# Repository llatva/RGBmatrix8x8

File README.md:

# RGBmatrix8x8
8x8 RGB matrix based on WS2813B addressable RGB leds

By Lasse Latva OH3HZB (2022)

This work is licensed under: Creative Commons Attribution 4.0 International (CC BY 4.0) https://creativecommons.org/licenses/by/4.0/

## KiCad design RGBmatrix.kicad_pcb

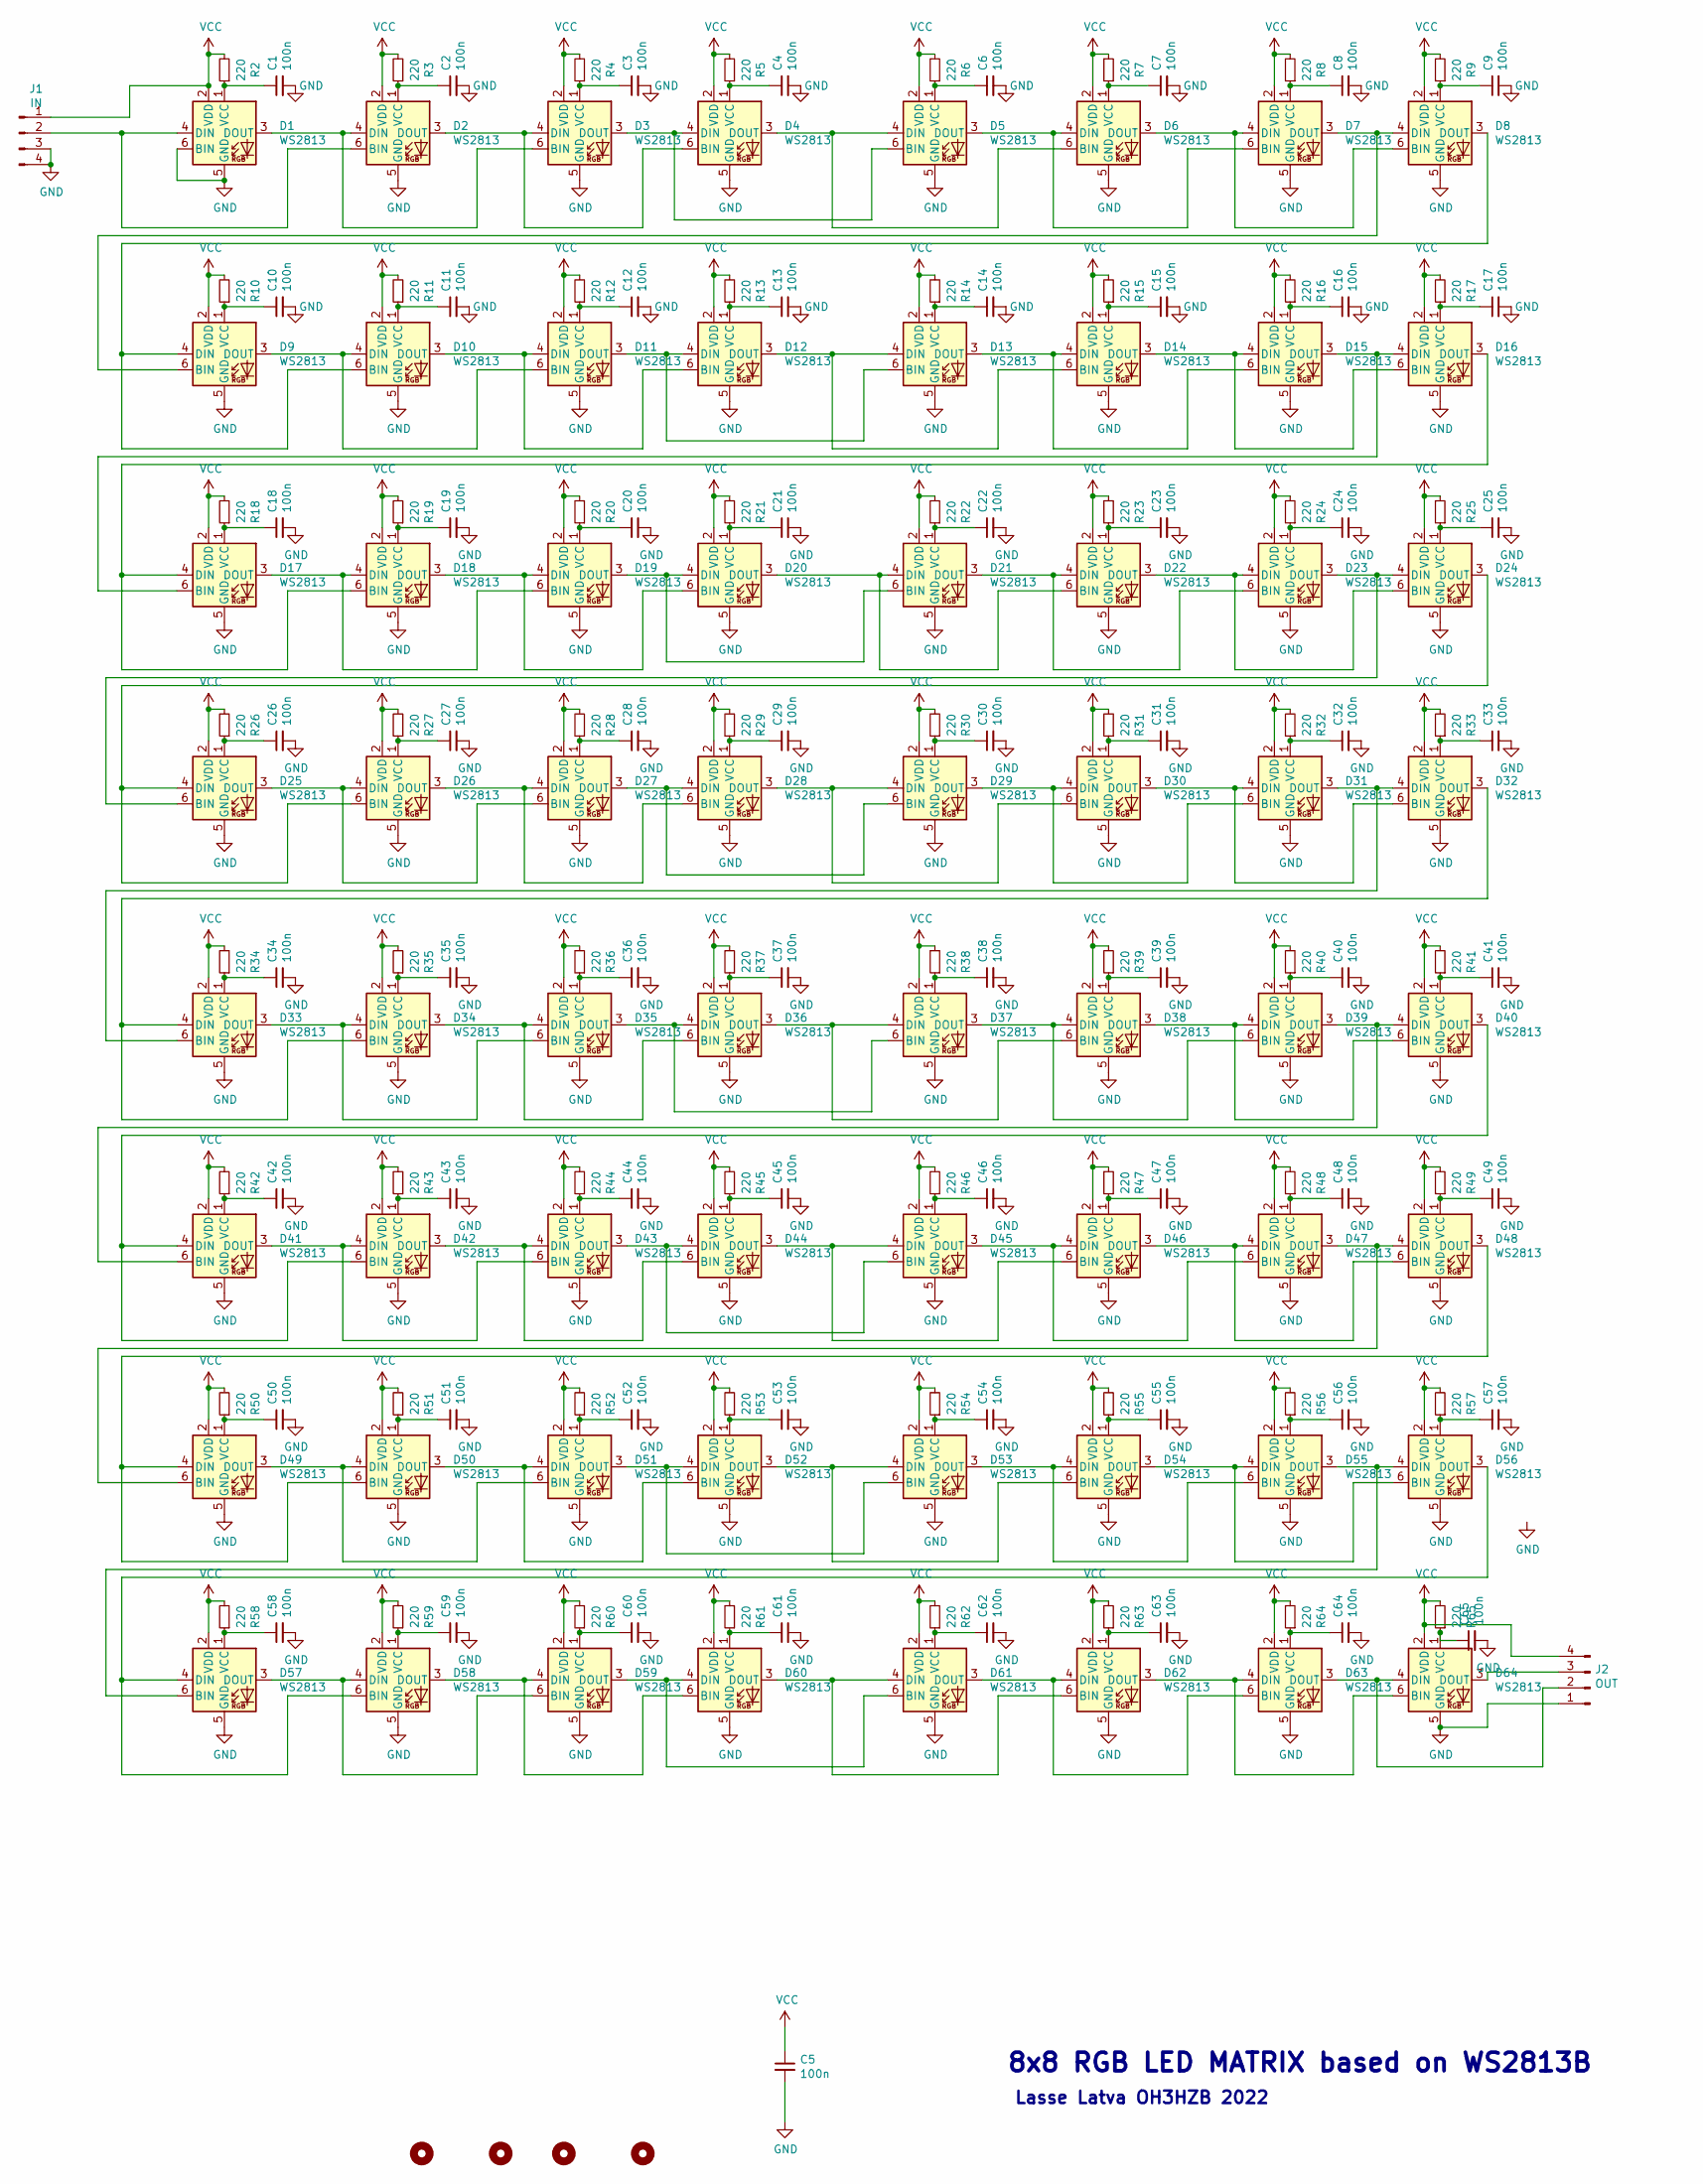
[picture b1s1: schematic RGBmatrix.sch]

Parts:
C1, C2, C3, C4, C5, C6, C7, C8, C9, C10, C11, C12, C13, C14, C15, C16, C17, C18, C19, C20, C21, C22, C23, C24, C25, C26, C27, C28, C29, C30, C31, C32, C33, C34, C35, C36, C37, C38, C39, C40, C41, C42, C43, C44, C45, C46, C47, C48, C49, C50, C51, C52, C53, C54, C55, C56, C57, C58, C59, C60, C61, C62, C63, C64, C65: 100n; C_0603_1608Metric; LCSC C49678
D1, D2, D3, D4, D5, D6, D7, D8, D9, D10, D11, D12, D13, D14, D15, D16, D17, D18, D19, D20, D21, D22, D23, D24, D25, D26, D27, D28, D29, D30, D31, D32, D33, D34, D35, D36, D37, D38, D39, D40, D41, D42, D43, D44, D45, D46, D47, D48, D49, D50, D51, D52, D53, D54, D55, D56, D57, D58, D59, D60, D61, D62, D63, D64: WS2813; LED_WS2812_PLCC6_5.0x5.0mm_P1.6mm; LCSC C114592
H1, H2, H3, H4: MountingHole; MountingHole_2.1mm
J1: IN; PinHeader_1x04_P2.54mm_Vertical
J2: OUT; PinHeader_1x04_P2.54mm_Vertical
R2, R3, R4, R5, R6, R7, R8, R9, R10, R11, R12, R13, R14, R15, R16, R17, R18, R19, R20, R21, R22, R23, R24, R25, R26, R27, R28, R29, R30, R31, R32, R33, R34, R35, R36, R37, R38, R39, R40, R41, R42, R43, R44, R45, R46, R47, R48, R49, R50, R51, R52, R53, R54, R55, R56, R57, R58, R59, R60, R61, R62, R63, R64, R65: 220; R_0603_1608Metric; LCSC C22962

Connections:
GND: C1.2, C2.2, C3.2, C4.2, C5.2, C6.2, C7.2, C8.2, C9.2, C10.2, C11.2, C12.2, C13.2, C14.2, C15.2, C16.2, C17.2, C18.2, C19.2, C20.2, C21.2, C22.2, C23.2, C24.2, C25.2, C26.2, C27.2, C28.2, C29.2, C30.2, C31.2, C32.2, C33.2, C34.2, C35.2, C36.2, C37.2, C38.2, C39.2, C40.2, C41.2, C42.2, C43.2, C44.2, C45.2, C46.2, C47.2, C48.2, C49.2, C50.2, C51.2, C52.2, C53.2, C54.2, C55.2, C56.2, C57.2, C58.2, C59.2, C60.2, C61.2, C62.2, C63.2, C64.2, C65.2, D1.5 (GND), D1.6 (BIN), D2.5 (GND), D3.5 (GND), D4.5 (GND), D5.5 (GND), D6.5 (GND), D7.5 (GND), D8.5 (GND), D9.5 (GND), D10.5 (GND), D11.5 (GND), D12.5 (GND), D13.5 (GND), D14.5 (GND), D15.5 (GND), D16.5 (GND), D17.5 (GND), D18.5 (GND), D19.5 (GND), D20.5 (GND), D21.5 (GND), D22.5 (GND), D23.5 (GND), D24.5 (GND), D25.5 (GND), D26.5 (GND), D27.5 (GND), D28.5 (GND), D29.5 (GND), D30.5 (GND), D31.5 (GND), D32.5 (GND), D33.5 (GND), D34.5 (GND), D35.5 (GND), D36.5 (GND), D37.5 (GND), D38.5 (GND), D39.5 (GND), D40.5 (GND), D41.5 (GND), D42.5 (GND), D43.5 (GND), D44.5 (GND), D45.5 (GND), D46.5 (GND), D47.5 (GND), D48.5 (GND), D49.5 (GND), D50.5 (GND), D51.5 (GND), D52.5 (GND), D53.5 (GND), D54.5 (GND), D55.5 (GND), D56.5 (GND), D57.5 (GND), D58.5 (GND), D59.5 (GND), D60.5 (GND), D61.5 (GND), D62.5 (GND), D63.5 (GND), D64.5 (GND), J1.3, J1.4, J2.1
unnamed: C1.1, D1.1 (VCC), R2.1
unnamed: C2.1, D2.1 (VCC), R3.1
unnamed: C3.1, D3.1 (VCC), R4.1
unnamed: C4.1, D4.1 (VCC), R5.1
unnamed: C6.1, D5.1 (VCC), R6.1
unnamed: C7.1, D6.1 (VCC), R7.1
unnamed: C8.1, D7.1 (VCC), R8.1
unnamed: C9.1, D8.1 (VCC), R9.1
unnamed: C10.1, D9.1 (VCC), R10.1
unnamed: C11.1, D10.1 (VCC), R11.1
unnamed: C12.1, D11.1 (VCC), R12.1
unnamed: C13.1, D12.1 (VCC), R13.1
unnamed: C14.1, D13.1 (VCC), R14.1
unnamed: C15.1, D14.1 (VCC), R15.1
unnamed: C16.1, D15.1 (VCC), R16.1
unnamed: C17.1, D16.1 (VCC), R17.1
unnamed: C18.1, D17.1 (VCC), R18.1
unnamed: C19.1, D18.1 (VCC), R19.1
unnamed: C20.1, D19.1 (VCC), R20.1
unnamed: C21.1, D20.1 (VCC), R21.1
unnamed: C22.1, D21.1 (VCC), R22.1
unnamed: C23.1, D22.1 (VCC), R23.1
unnamed: C24.1, D23.1 (VCC), R24.1
unnamed: C25.1, D24.1 (VCC), R25.1
unnamed: C26.1, D25.1 (VCC), R26.1
unnamed: C27.1, D26.1 (VCC), R27.1
unnamed: C28.1, D27.1 (VCC), R28.1
unnamed: C29.1, D28.1 (VCC), R29.1
unnamed: C30.1, D29.1 (VCC), R30.1
unnamed: C31.1, D30.1 (VCC), R31.1
unnamed: C32.1, D31.1 (VCC), R32.1
unnamed: C33.1, D32.1 (VCC), R33.1
unnamed: C34.1, D33.1 (VCC), R34.1
unnamed: C35.1, D34.1 (VCC), R35.1
unnamed: C36.1, D35.1 (VCC), R36.1
unnamed: C37.1, D36.1 (VCC), R37.1
unnamed: C38.1, D37.1 (VCC), R38.1
unnamed: C39.1, D38.1 (VCC), R39.1
unnamed: C40.1, D39.1 (VCC), R40.1
unnamed: C41.1, D40.1 (VCC), R41.1
unnamed: C42.1, D41.1 (VCC), R42.1
unnamed: C43.1, D42.1 (VCC), R43.1
unnamed: C44.1, D43.1 (VCC), R44.1
unnamed: C45.1, D44.1 (VCC), R45.1
unnamed: C46.1, D45.1 (VCC), R46.1
unnamed: C47.1, D46.1 (VCC), R47.1
unnamed: C48.1, D47.1 (VCC), R48.1
unnamed: C49.1, D48.1 (VCC), R49.1
unnamed: C50.1, D49.1 (VCC), R50.1
unnamed: C51.1, D50.1 (VCC), R51.1
unnamed: C52.1, D51.1 (VCC), R52.1
unnamed: C53.1, D52.1 (VCC), R53.1
unnamed: C54.1, D53.1 (VCC), R54.1
unnamed: C55.1, D54.1 (VCC), R55.1
unnamed: C56.1, D55.1 (VCC), R56.1
unnamed: C57.1, D56.1 (VCC), R57.1
unnamed: C58.1, D57.1 (VCC), R58.1
unnamed: C59.1, D58.1 (VCC), R59.1
unnamed: C60.1, D59.1 (VCC), R60.1
unnamed: C61.1, D60.1 (VCC), R61.1
unnamed: C62.1, D61.1 (VCC), R62.1
unnamed: C63.1, D62.1 (VCC), R63.1
unnamed: C64.1, D63.1 (VCC), R64.1
unnamed: C65.1, D64.1 (VCC), R65.1
unnamed: D1.3 (DOUT), D2.4 (DIN), D3.6 (BIN)
unnamed: D1.4 (DIN), D2.6 (BIN), J1.2
unnamed: D2.3 (DOUT), D3.4 (DIN), D4.6 (BIN)
unnamed: D3.3 (DOUT), D4.4 (DIN), D5.6 (BIN)
unnamed: D4.3 (DOUT), D5.4 (DIN), D6.6 (BIN)
unnamed: D5.3 (DOUT), D6.4 (DIN), D7.6 (BIN)
unnamed: D6.3 (DOUT), D7.4 (DIN), D8.6 (BIN)
unnamed: D7.3 (DOUT), D8.4 (DIN), D9.6 (BIN)
unnamed: D10.3 (DOUT), D11.4 (DIN), D12.6 (BIN)
unnamed: D9.3 (DOUT), D10.4 (DIN), D11.6 (BIN)
unnamed: D8.3 (DOUT), D9.4 (DIN), D10.6 (BIN)
unnamed: D11.3 (DOUT), D12.4 (DIN), D13.6 (BIN)
unnamed: D12.3 (DOUT), D13.4 (DIN), D14.6 (BIN)
unnamed: D13.3 (DOUT), D14.4 (DIN), D15.6 (BIN)
unnamed: D14.3 (DOUT), D15.4 (DIN), D16.6 (BIN)
unnamed: D15.3 (DOUT), D16.4 (DIN), D17.6 (BIN)
unnamed: D16.3 (DOUT), D17.4 (DIN), D18.6 (BIN)
unnamed: D17.3 (DOUT), D18.4 (DIN), D19.6 (BIN)
unnamed: D18.3 (DOUT), D19.4 (DIN), D20.6 (BIN)
unnamed: D19.3 (DOUT), D20.4 (DIN), D21.6 (BIN)
unnamed: D20.3 (DOUT), D21.4 (DIN), D22.6 (BIN)
unnamed: D21.3 (DOUT), D22.4 (DIN), D23.6 (BIN)
unnamed: D22.3 (DOUT), D23.4 (DIN), D24.6 (BIN)
unnamed: D23.3 (DOUT), D24.4 (DIN), D25.6 (BIN)
unnamed: D24.3 (DOUT), D25.4 (DIN), D26.6 (BIN)
unnamed: D25.3 (DOUT), D26.4 (DIN), D27.6 (BIN)
unnamed: D26.3 (DOUT), D27.4 (DIN), D28.6 (BIN)
unnamed: D27.3 (DOUT), D28.4 (DIN), D29.6 (BIN)
unnamed: D28.3 (DOUT), D29.4 (DIN), D30.6 (BIN)
unnamed: D29.3 (DOUT), D30.4 (DIN), D31.6 (BIN)
unnamed: D30.3 (DOUT), D31.4 (DIN), D32.6 (BIN)
unnamed: D31.3 (DOUT), D32.4 (DIN), D33.6 (BIN)
unnamed: D32.3 (DOUT), D33.4 (DIN), D34.6 (BIN)
unnamed: D33.3 (DOUT), D34.4 (DIN), D35.6 (BIN)
unnamed: D34.3 (DOUT), D35.4 (DIN), D36.6 (BIN)
unnamed: D35.3 (DOUT), D36.4 (DIN), D37.6 (BIN)
unnamed: D36.3 (DOUT), D37.4 (DIN), D38.6 (BIN)
unnamed: D37.3 (DOUT), D38.4 (DIN), D39.6 (BIN)
unnamed: D38.3 (DOUT), D39.4 (DIN), D40.6 (BIN)
unnamed: D39.3 (DOUT), D40.4 (DIN), D41.6 (BIN)
unnamed: D40.3 (DOUT), D41.4 (DIN), D42.6 (BIN)
unnamed: D41.3 (DOUT), D42.4 (DIN), D43.6 (BIN)
unnamed: D42.3 (DOUT), D43.4 (DIN), D44.6 (BIN)
unnamed: D43.3 (DOUT), D44.4 (DIN), D45.6 (BIN)
unnamed: D44.3 (DOUT), D45.4 (DIN), D46.6 (BIN)
unnamed: D45.3 (DOUT), D46.4 (DIN), D47.6 (BIN)
unnamed: D46.3 (DOUT), D47.4 (DIN), D48.6 (BIN)
unnamed: D47.3 (DOUT), D48.4 (DIN), D49.6 (BIN)
unnamed: D48.3 (DOUT), D49.4 (DIN), D50.6 (BIN)
unnamed: D49.3 (DOUT), D50.4 (DIN), D51.6 (BIN)
unnamed: D50.3 (DOUT), D51.4 (DIN), D52.6 (BIN)
unnamed: D51.3 (DOUT), D52.4 (DIN), D53.6 (BIN)
unnamed: D52.3 (DOUT), D53.4 (DIN), D54.6 (BIN)
unnamed: D53.3 (DOUT), D54.4 (DIN), D55.6 (BIN)
unnamed: D54.3 (DOUT), D55.4 (DIN), D56.6 (BIN)
unnamed: D55.3 (DOUT), D56.4 (DIN), D57.6 (BIN)
unnamed: D56.3 (DOUT), D57.4 (DIN), D58.6 (BIN)
unnamed: D57.3 (DOUT), D58.4 (DIN), D59.6 (BIN)
unnamed: D58.3 (DOUT), D59.4 (DIN), D60.6 (BIN)
unnamed: D59.3 (DOUT), D60.4 (DIN), D61.6 (BIN)
unnamed: D60.3 (DOUT), D61.4 (DIN), D62.6 (BIN)
unnamed: D61.3 (DOUT), D62.4 (DIN), D63.6 (BIN)
unnamed: D62.3 (DOUT), D63.4 (DIN), D64.6 (BIN)
unnamed: D63.3 (DOUT), D64.4 (DIN), J2.2
unnamed: D64.3 (DOUT), J2.3
VCC: C5.1, D1.2 (VDD), D2.2 (VDD), D3.2 (VDD), D4.2 (VDD), D5.2 (VDD), D6.2 (VDD), D7.2 (VDD), D8.2 (VDD), D9.2 (VDD), D10.2 (VDD), D11.2 (VDD), D12.2 (VDD), D13.2 (VDD), D14.2 (VDD), D15.2 (VDD), D16.2 (VDD), D17.2 (VDD), D18.2 (VDD), D19.2 (VDD), D20.2 (VDD), D21.2 (VDD), D22.2 (VDD), D23.2 (VDD), D24.2 (VDD), D25.2 (VDD), D26.2 (VDD), D27.2 (VDD), D28.2 (VDD), D29.2 (VDD), D30.2 (VDD), D31.2 (VDD), D32.2 (VDD), D33.2 (VDD), D34.2 (VDD), D35.2 (VDD), D36.2 (VDD), D37.2 (VDD), D38.2 (VDD), D39.2 (VDD), D40.2 (VDD), D41.2 (VDD), D42.2 (VDD), D43.2 (VDD), D44.2 (VDD), D45.2 (VDD), D46.2 (VDD), D47.2 (VDD), D48.2 (VDD), D49.2 (VDD), D50.2 (VDD), D51.2 (VDD), D52.2 (VDD), D53.2 (VDD), D54.2 (VDD), D55.2 (VDD), D56.2 (VDD), D57.2 (VDD), D58.2 (VDD), D59.2 (VDD), D60.2 (VDD), D61.2 (VDD), D62.2 (VDD), D63.2 (VDD), D64.2 (VDD), J1.1, J2.4, R2.2, R3.2, R4.2, R5.2, R6.2, R7.2, R8.2, R9.2, R10.2, R11.2, R12.2, R13.2, R14.2, R15.2, R16.2, R17.2, R18.2, R19.2, R20.2, R21.2, R22.2, R23.2, R24.2, R25.2, R26.2, R27.2, R28.2, R29.2, R30.2, R31.2, R32.2, R33.2, R34.2, R35.2, R36.2, R37.2, R38.2, R39.2, R40.2, R41.2, R42.2, R43.2, R44.2, R45.2, R46.2, R47.2, R48.2, R49.2, R50.2, R51.2, R52.2, R53.2, R54.2, R55.2, R56.2, R57.2, R58.2, R59.2, R60.2, R61.2, R62.2, R63.2, R64.2, R65.2

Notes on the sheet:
8x8 RGB LED MATRIX based on WS2813B
Lasse Latva OH3HZB 2022

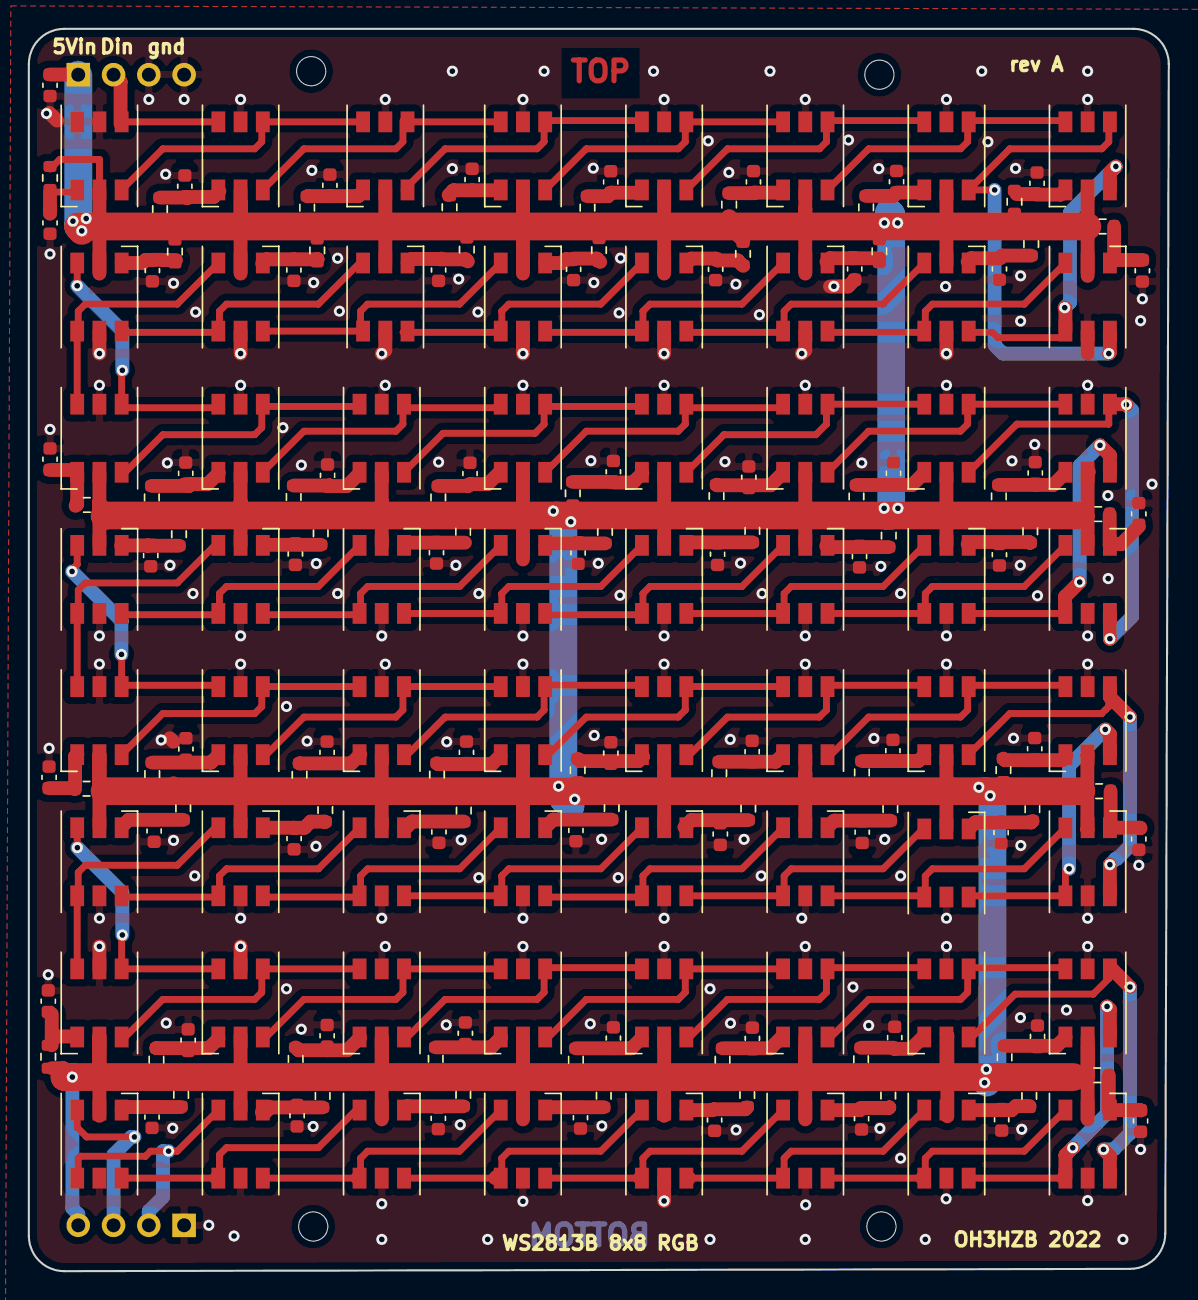
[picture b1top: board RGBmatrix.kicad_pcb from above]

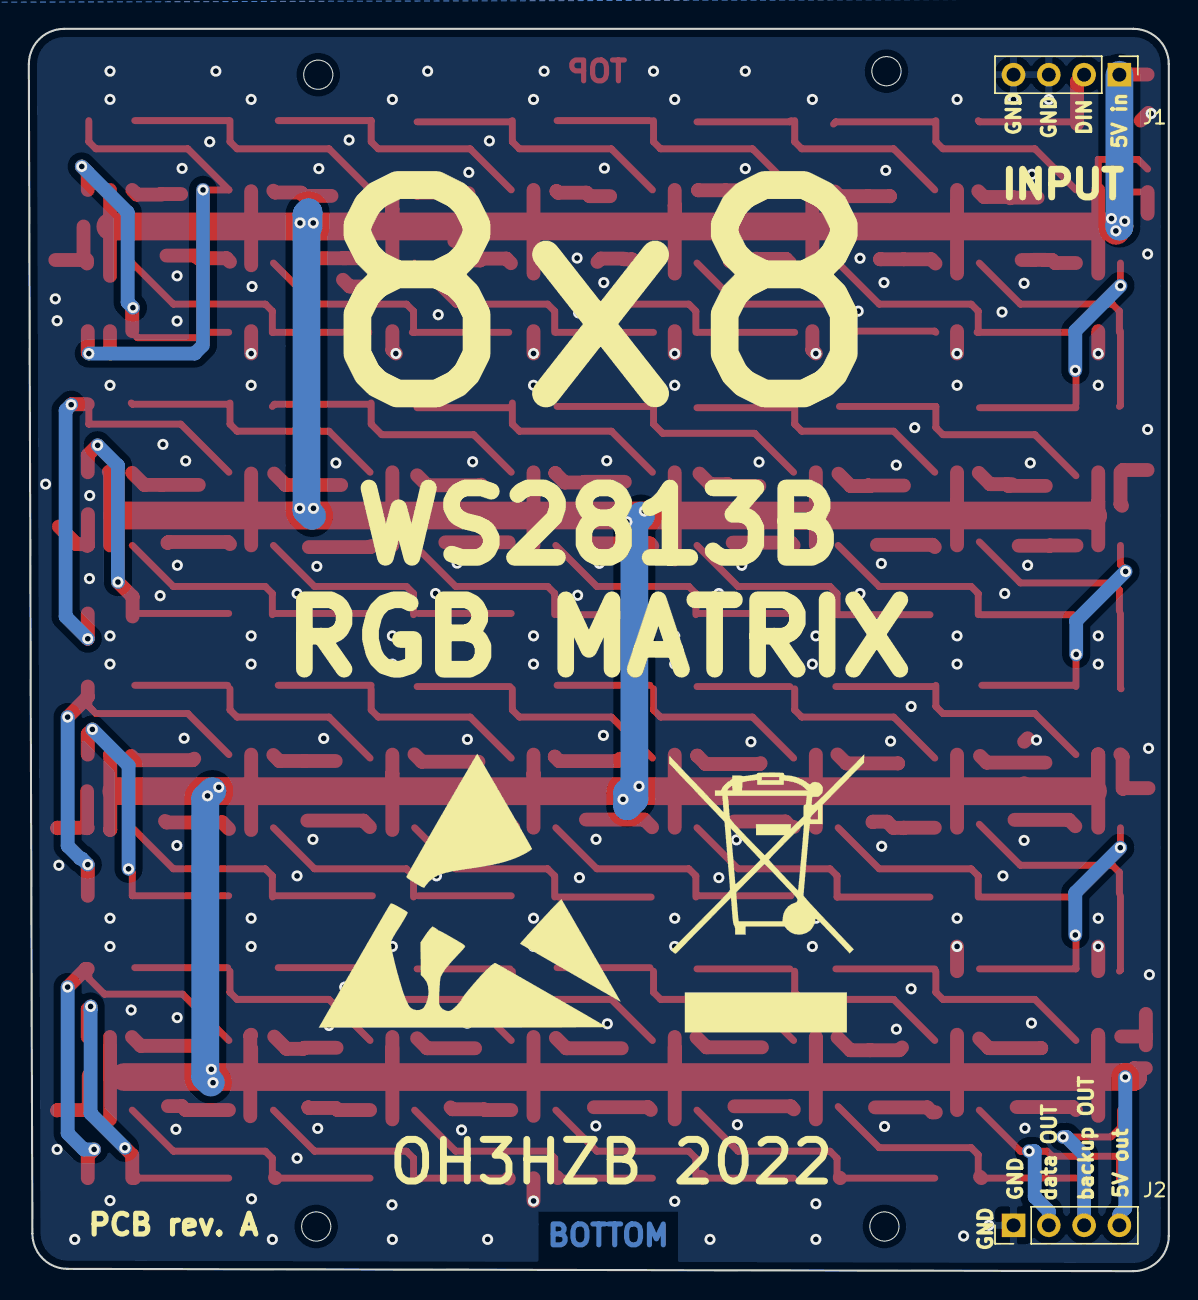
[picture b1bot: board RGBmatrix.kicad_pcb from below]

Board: 2 copper layers, 82.0 x 89.4 mm, 199 parts (2 on the bottom side), 131 nets.

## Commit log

2022-01-28 initial commit to github
2022-01-28 cropped
